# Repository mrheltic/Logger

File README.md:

# Logger

## 📝 Table of Contents
- [About](#🧐-about)
- [Getting Started](#🏁-getting-started)
- [Hardware](#🔧-hardware-required)
- [Description](#description)
- [Theoretical Notions](#theoretical-notions)
- [Code](#⌨️-code)
- [Display Mode](#🖥️-display-mode)
- [SD Mode](#💾-sd-mode)
- [Serial Mode](#💻-serial-mode)
- [Built using](#⛏️-built-using)
- [Contributing](#🫂-contributing)
- [Authors](#✍️-authors)
- [Repo Activity](#repo-activity)
- [License](#license)
- [Acknowledgments](#🎉-acknowledgments)

## 🧐 About
This project is a data acquisition system built using an ESP32 microcontroller board. The system incorporates an ADS1115 analog-to-digital converter, an SSD1306 display, and three buttons for user interaction. It is designed to store data on an SD card or send it to a pc for further analysis.

### Features

- Acquisition of analog sensor data using ADS1115 ADC
- Real-time display of sensor readings on SSD1306 OLED display
- User interaction through three buttons for control and configuration
- Storage of acquired data on an SD card for offline access
- Transmission of data to a computer for centralized analysis

## 🔧 Hardware Required

## 🏁 Getting Started

### Prerequisites

- Arduino IDE or Visual Studio Code (with PlatformIO)
- ESP32 board manager for Arduino IDE
- Libraries:
  - Adafruit ADS1X15 (for ADS1115)
  - Adafruit SSD1306 (for SSD1306 display)
  - SD (for SD card storage)
  - <other libraries as required>

### Installation

<details open>
<summary><i>Installation using Arduino IDE</i></summary>

- Clone or download the project repository from GitHub.
- Open the Arduino IDE and install the ESP32 board manager if not already installed.
- Connect the hardware components as per the provided circuit diagram.
- Install the required libraries using the Arduino Library Manager.
- Upload the code to the ESP32 board using the Arduino IDE.
- Monitor the serial output to ensure successful connection to the sensors.
- Verify the functionality by checking the sensor readings on the SSD1306 display and the data storage on the SD card.
</details>

<details open>
<summary><i>Installation using Visual Studio Code</i></summary>

- Clone or download the project repository from GitHub.
- Open VS and compile the software (changing the details on platform.ini according to your hardware).
- Connect the hardware components as per the provided circuit diagram.
- Upload the code to the ESP32 board using the upload tool.
- Monitor the serial output to ensure successful connection to the sensors.
- Verify the functionality by checking the sensor readings on the SSD1306 display and the data storage on the SD card.

</details>

## Description

## ⌨️ Code

All the code was written using the arduino Framework, for an ESP32. This gave us significant advantages in terms of ease of writing, online documentation, and especially in terms of click-through, which is considerably greater than for an arduino Uno. We followed a kind of MVC model, where each component is separate from the others and deals only with the things it is responsible for, invoking higher-level primitives. This allowed us to manage different components more smoothly.

### Main

The main substantially is a method wrapper and deals at a higher level with handling scrolling through the various menus. Initially (in setup) it asks the controller to initialize devices (the basic ones, such as buttons, screen, ...)

```cpp
while (!initializeDevices()){
}

updateMenu();
```

After this handles menu selection

```cpp
if (stateMenu)
{
  if (goDown())
  {
    menu++;
  }
  if (goUp())
  {
    menu--;
  }
  if (select())
  {
    executeAction(); //Enters in the selected menu
  }
}
```

### Controller

The controller is the component that manages all component behavior and is directly responsible for making measurements. Besides that it initializes all the devices and the serial. The initializations that are done can be blocking or non-blocking, depending on the type of component we want to initialize: a failure of the fundamental components results in a program block inside a loop, which will not allow the execution of the remaining code, while the other components may not be initialized at all. The reference with respect to the success or failure of initialization we have it by returning a boolean value true when the method is terminated, so it does not take into account subsequent failures. The whole initial part is devoted to declaring all pins connected to the board, and in case of custom configurations they can be changed before compilation. 

After all parameters have been selected, data acquisition will proceed. This involves an initial setup phase, in which, based on what parameters are selected (saved as global variables in the controller) it will go to set the mode (and consequently the channels to read from), the data rate, and calculate gain and offset. Depending on the output selected it could change significantly, but we will also have an output on the serial that tells us what is happening. Also in this part I am going to initialize the measurement object, which will handle the calculations made for mean and std.

```cpp
void adcSetup()
{
  setRate(currentSampleRate); //Physically setting the sample rate with ADS function
  setChannel(); //Setting the channel, gain and other useful parameters

  K_value = calculateCoefficient();
  O_value = calculateOffset();

  Measurement measurement(currentSampleRate); //Instantiate the object
}
```

After running the setup you enter the loggerAct, which is the method that takes care of the measurement. Here, depending on the mode that will be selected it will have different behavior, but basically what it does is:

```cpp
// The microcontroller is waiting for an interrupt from the ADC
if (!new_data)
  {
    return;
  }

// When the adc is alerted via the alert pin the code continues

if (!measurement.isArrayFull())
  {
    measurement.insertMeasurement(adcValue); // Get the misuration and stores in the array
  }

else
  {
    measurement.setArrayFull(false); // Empties the array and compute mean and std
    loggerGraphic(mode, channel, timestamp, mean); // Print on display the parameters
  }

new_data = false;
```

### View

The view component deals with screen management. Here it is initialized and passing it the necessary parameters updates the screen. Bipmap images of the various modes and associated sliders are also saved here. The view also provides functions to be used directly by the controller, such as the one used during the loggerAct, which takes care of printing media (for each second), timestamp, mode, and output

### Model

The model is the component that manages the "measurements" class and takes care of the array. This provides various functions to calculate different values useful for measurements, such as mean and standard deviation. In fact, when we go to initialize the object an array is created, of length equal to the data rate, and we go to calculate mean and std for each second. Each time the adc returns us the value, from the controller, we go to invoke a function that is used to insert the measured value (already possibly multiplied by the gain and summed with the offset) at the tail of the array. 

```cpp
class Measurement
{
private:
    int *measurements;
    float mean;
    float std; 
    bool arrayFull;

public:
    Measurement(int len);
    ~Measurement();
    void insertMeasurement(int value);
    void calculateMean();
    void calculateStd();
    void reset();
    bool isArrayFull();
    int getLength();
};
```

## Theoretical Notions
<details open>
<summary><i>Adc</i></summary>
In this project we use the ADS1115 that is a very small, low-power, 16-bit, delta-sigma (ΔΣ) analog-to-digital converters (ADCs).
There are many ADCs available on the market for various applications: Ramping, SAR, delta-sigma, Flash and so on. 
ΔΣ ADCs are now ideal for converting analog signals over a wide range of frequencies, from DC to several megahertz. Basically, these converters consist of an oversampling modulator followed by a digital filter that together produce a high-resolution data-stream output. The ADS1115 has an adjustable gain(PGA), an interal voltage reference, a clock oscillator, an I2C interface, and also a programmable digital comparator that provides an alert on a dedicated pin. The latter played an important role in carrying out the sampling at the maximum achievable speed of 860SPS. Thanks to the mux the adc has four single-ended(to measure
each channel with respect to ground) or two differential inputs and two available conversion mode: single-shot mode(power saving mode) and continuous mode. In continuous conversion mode, the adc automatically begins a conversion of the input as soon as the previous conversion is completed and the rate is programmed by software.
To achieve high accuracy measurements it's a mandatory following several step:

- Use the Maximum Resolution in the readings
- Adjust the PGA to match the voltage range of your input signal(all specifications can be found in the datasheet)
- Use an external voltage reference instead of the integrated
- Implement appropriate filtering and signal conditioning techniques to minimize noise and Interference
- Periodically calibrate the system to compensate any drift
- Avoid common source of error such as impedance mismatches
- Select data rate based on dynamic meausurements or slow signals
- Minimize signal path lengths.
</details>

## 🖥️ Display Mode

### Usage

### Performance Evaluation

## 💾 SD Mode

### Usage

### Performance Evaluation

## 💻 Serial Mode

### Usage

### Explanation

In the data acquisition stage, data is sent to the pc, which is processed through python. The manufacturer of the module, in the datasheet indicates that the conversion time is exactly equivalent to 1/DR (worst case: 860SPS), so there will certainly be a small delay due to data processing due to the microcontroller. This, in turn, will have to be added to a time, albeit very small, due to communication via serial. We had initially opted to send the data via the `Serial.println()` function, but this route, following some testing, seemed impractical. This was because, while having a readable result directly from the serial would have made it easy and intuitive to retrieve the data, it introduced a considerable delay, far in excess of the 1/DR value, even orders of magnitude (about tenths of a second). We therefore opted for the `Serial.write()` function, but again there were problems, since the measured values are 16-bit integers, so they needed to be split in two and sent (so as to send 8 bits at a time). 

```cpp
Serial.write(0xCC);                   // Start byte
Serial.write((ADCvalue >> 8) & 0xFF); // High byte
Serial.write(ADCvalue & 0xFF);       // Low byte
```
- `Serial.write(0xCC)` sends a start byte. The Serial.write() function writes binary data to the serial port. 0xCC is the hexadecimal representation of the start byte. The microcontroller need to send this to communicate that a new set of data is starting.

- `Serial.write((ADCvalue >> 8) & 0xFF)` sends the high byte of ADCvalue. The >> 8 operation shifts the bits of ADCvalue 8 places to the right, effectively moving the high byte to the position of the low byte. The & 0xFF operation then masks the lower byte, so only the original high byte of ADCvalue remains.

- `Serial.write(ADCvalue & 0xFF)` sends the low byte of ADCvalue. The & 0xFF operation masks the high byte of ADCvalue, so only the low byte remains.

After the microcontroller sends the measured value this way, python will have to deal with reconstructing it and converting it to a readable value, like this:

```python
start_byte = ser.read(1)  # Read the start byte
    if start_byte == b'\xCC':  # Verify the start byte
        high_byte = ser.read(1)  # Read the high byte
        low_byte = ser.read(1)  # Read the low byte
        measurement = (ord(high_byte) << 8) | ord(low_byte)  # Merge the bytes
```

- `start_byte = ser.read(1)` reads one byte from the serial port and assigns it to the variable start_byte.

- `if start_byte == b'\xCC'` checks if the start byte is equal to b'\xCC', which is the byte representation of the hexadecimal number 0xCC. If the start byte is 0xCC, the code inside the if statement will be executed. This is used to verify that the data transmission is starting correctly.

- `high_byte = ser.read(1)` reads the next byte (after the start byte) from the serial port, which is the high byte of the measurement.

- `low_byte = ser.read(1)` reads the next byte from the serial port, which is the low byte of the measurement.

- `measurement = (ord(high_byte) << 8) | ord(low_byte)` merges the high byte and the low byte to reconstruct the original measurement. The `ord()` function is used to get the integer value of a byte. The `<< 8` operation shifts the bits of the high byte 8 places to the left, effectively moving it to the position of the high byte in a 16-bit number. The `|` operation is a bitwise OR, which combines the high byte and the low byte into a single 16-bit number.

For more in-depth information you can visit the python code repository directly: [Serial Mode Logger](https://github.com/mrheltic/Serial-Mode-Logger)

### Performance Evaluation

## ⛏️ Built Using
- [PlatformIO](https://platformio.org) - PlatformIO
- [Arduino Framework](https://www.arduino.cc) - Arduino Framework

## 🫂 Contributing

Contributions to this project are welcome. If you encounter any issues or have ideas for improvements, please submit a pull request or open an issue on the project repository.

## ✍️ Authors
- [@mrheltic](https://github.com/mrheltic) - Florio Vincenzo Pio
- [@Phersax](https://github.com/Phersax) - Stasi Francesco
- [@murcie443](https://github.com/murcie443) - Tonti Davide

## Repo Activity

## License
Details about the license.

## 🎉 Acknowledgments
Any acknowledgments (optional).

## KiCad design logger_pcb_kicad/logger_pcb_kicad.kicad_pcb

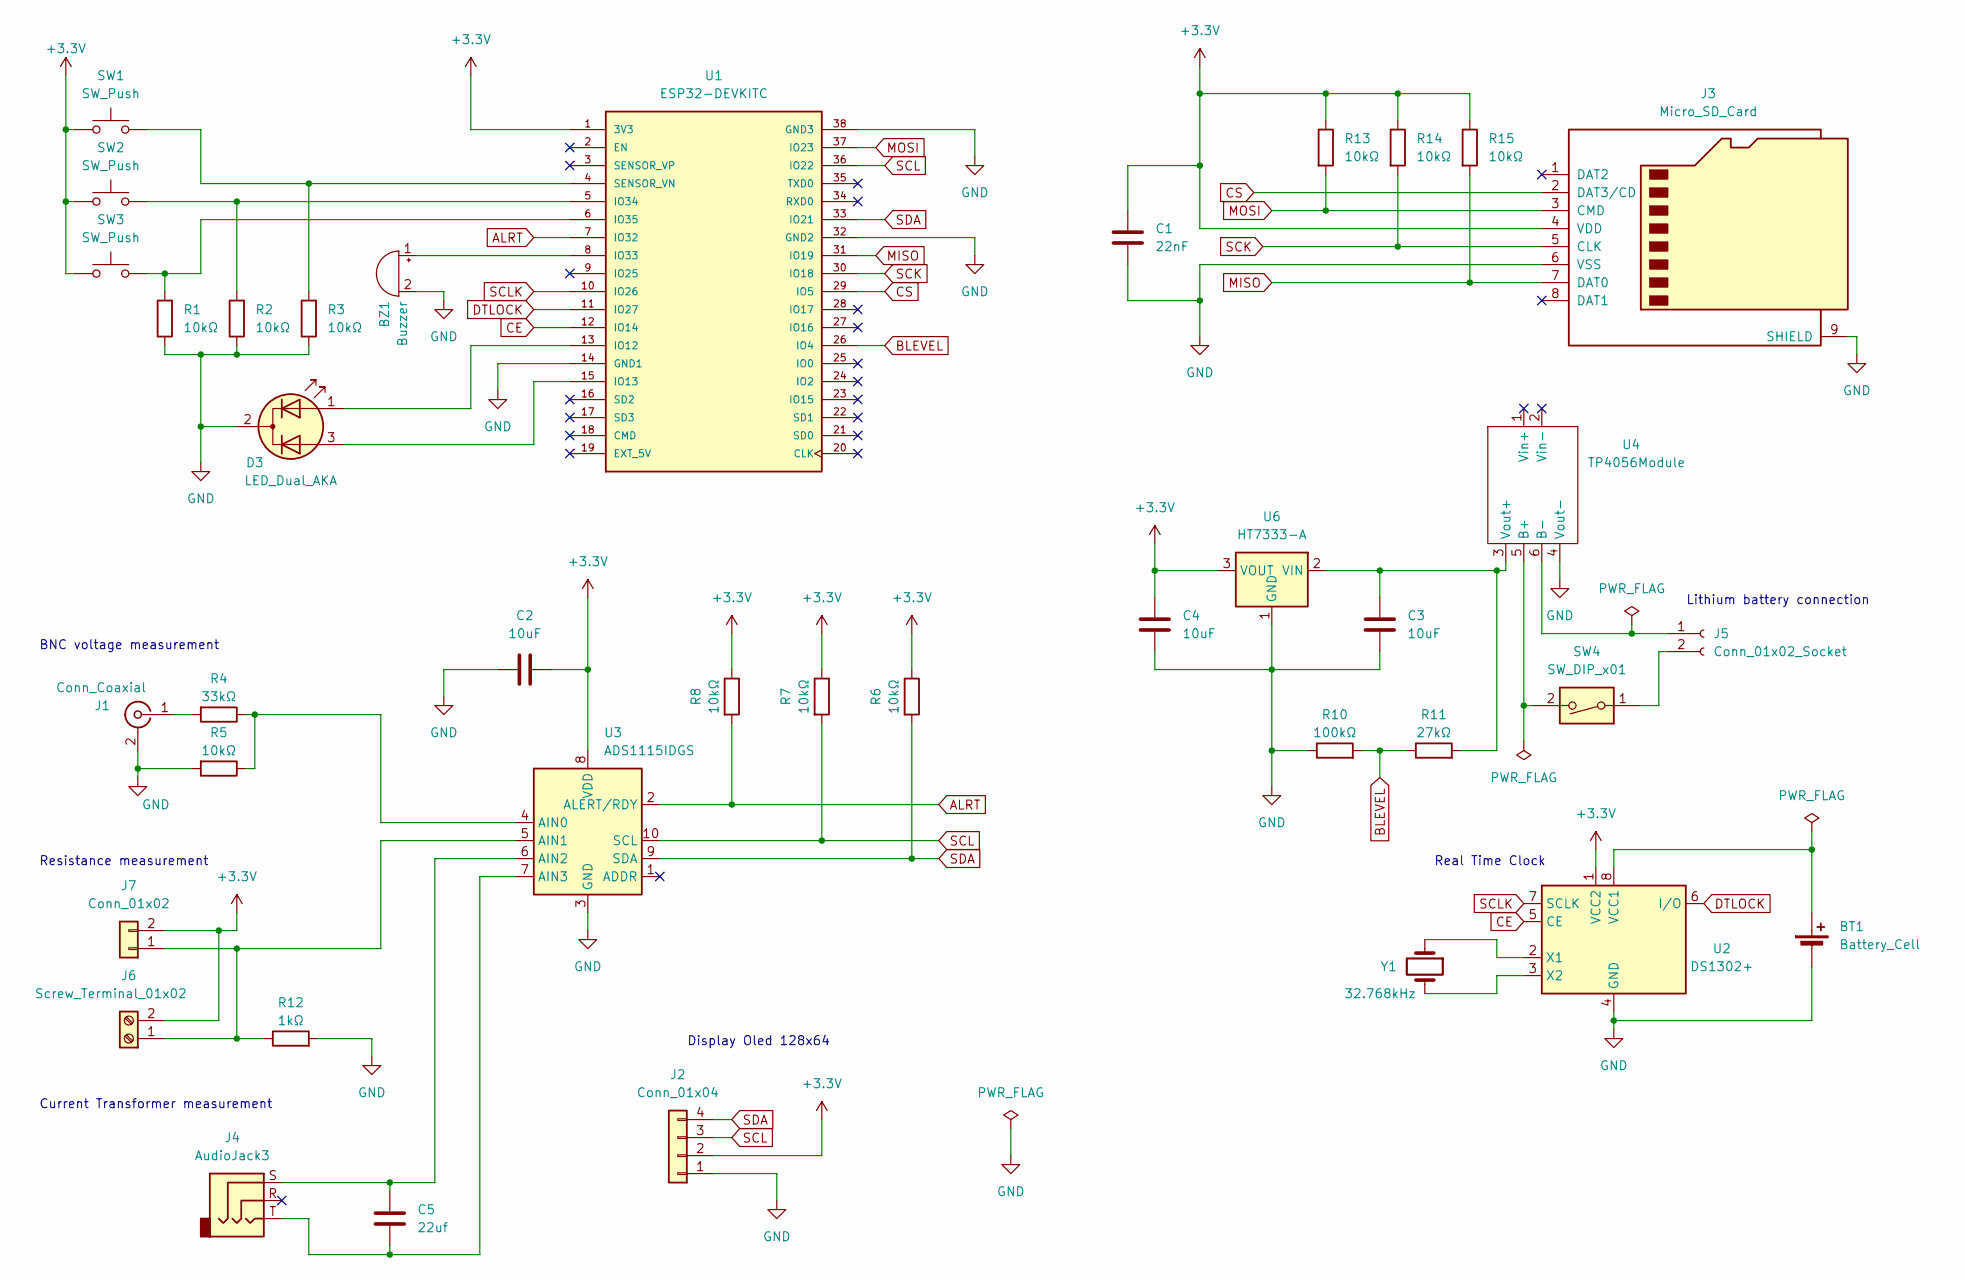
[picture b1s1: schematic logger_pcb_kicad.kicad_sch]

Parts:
BT1: Battery_Cell; Battery_holder_cr2032
BZ1: Buzzer; Buzzer_12x9.5RM7.6
C1: 22nF; C_0805_2012Metric
C2, C3, C4: 10uF; C_0805_2012Metric
C5: 22uf; C_0805_2012Metric
D3: LED_Dual_AKA; LED_D3.0mm-3
J1: Conn_Coaxial; BNC_TEConnectivity_1478035_Horizontal
J2: Conn_01x04; 128x64OLED
J3: Micro_SD_Card; J_SD_Card-micro_socket_A
J4: AudioJack3; Jack_3.5mm_CUI_SJ1-3525N_Horizontal
J5: Conn_01x02_Socket; JST_EH_B2B-EH-A_1x02_P2.50mm_Vertical
J6: Screw_Terminal_01x02; TerminalBlock_Altech_AK300-2_P5.00mm
J7: Conn_01x02; PinHeader_1x02_P2.54mm_Vertical
R1, R2, R3, R6, R7, R8, R13, R14, R15: 10kΩ; R_1206_3216Metric
R4: 33kΩ; R_Axial_DIN0207_L6.3mm_D2.5mm_P10.16mm_Horizontal
R5: 10kΩ; R_Axial_DIN0207_L6.3mm_D2.5mm_P10.16mm_Horizontal
R10: 100kΩ; R_Axial_DIN0207_L6.3mm_D2.5mm_P10.16mm_Horizontal
R11: 27kΩ; R_Axial_DIN0207_L6.3mm_D2.5mm_P10.16mm_Horizontal
R12: 1kΩ; R_Axial_DIN0207_L6.3mm_D2.5mm_P10.16mm_Horizontal
SW1, SW2, SW3: SW_Push; SW_PUSH-12mm
SW4: SW_DIP_x01; SW_CuK_JS202011AQN_DPDT_Angled
U1: ESP32-DEVKITC; MODULE_ESP32-DEVKITC; PARTREV N/A
U2: DS1302+; DIP-8_W7.62mm
U3: ADS1115IDGS; TSSOP-10_3x3mm_P0.5mm
U4: TP4056Module; TP4056-18650
U6: HT7333-A; SOT-89-3
Y1: 32.768kHz; Crystal_C38-LF_D3.0mm_L8.0mm_Horizontal

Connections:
+3.3V: C1.1, C2.1, C4.1, J2.2, J3.4 (VDD), J6.2, J7.2, R6.1, R7.1, R8.1, R13.1, R14.1, R15.1, SW1.1, SW2.1, SW3.1, U1.1 (3V3), U2.1 (VCC2), U3.8 (VDD), U6.3 (VOUT)
ALRT: R8.2, U1.7 (IO32), U3.2 (ALERT/RDY)
BLEVEL: R10.2, R11.1, U1.26 (IO4)
CE: U1.12 (IO14), U2.5 (CE)
CS: J3.2 (DAT3/CD), U1.29 (IO5)
DTLOCK: U1.11 (IO27), U2.6 (I/O)
GND: BT1.2 (-), BZ1.2 (+), C1.2, C2.2, C3.2, C4.2, D3.2 (K), J1.2 (Ext), J2.1, J3.6 (VSS), J3.9 (SHIELD), R1.1, R2.1, R3.1, R5.2, R10.1, R12.2, U1.14 (GND1), U1.32 (GND2), U1.38 (GND3), U2.4 (GND), U3.3 (GND), U4.4 (Vout-), U6.1 (GND)
MISO: J3.7 (DAT0), R15.2, U1.31 (IO19)
MOSI: J3.3 (CMD), R13.2, U1.37 (IO23)
unnamed: BT1.1 (+), U2.8 (VCC1)
unnamed: BZ1.1 (-), U1.8 (IO33)
unnamed: D3.1 (A1), U1.13 (IO12)
unnamed: D3.3 (A2), U1.15 (IO13)
unnamed: J1.1 (In), R4.2
unnamed: J5.1, U4.6 (B-)
unnamed: J5.2, SW4.1
unnamed: J6.1, J7.1, R12.1, U3.5 (AIN1)
unnamed: R2.2, SW2.2, U1.5 (IO34)
unnamed: R1.2, SW3.2, U1.6 (IO35)
unnamed: R3.2, SW1.2, U1.4 (SENSOR_VN)
unnamed: U2.2 (X1), Y1.1
unnamed: U2.3 (X2), Y1.2
unnamed: R4.1, R5.1, U3.4 (AIN0)
unnamed: C5.1, J4.S, U3.6 (AIN2)
unnamed: C5.2, J4.T, U3.7 (AIN3)
unnamed: SW4.2, U4.5 (B+)
unnamed: C3.1, R11.2, U4.3 (Vout+), U6.2 (VIN)
SCK: J3.5 (CLK), R14.2, U1.30 (IO18)
SCL: J2.3, R7.2, U1.36 (IO22), U3.10 (SCL)
SCLK: U1.10 (IO26), U2.7 (SCLK)
SDA: J2.4, R6.2, U1.33 (IO21), U3.9 (SDA)

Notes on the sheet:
BNC voltage measurement
Real Time Clock
Current Transformer measurement
Resistance measurement
Display Oled 128x64
Lithium battery connection

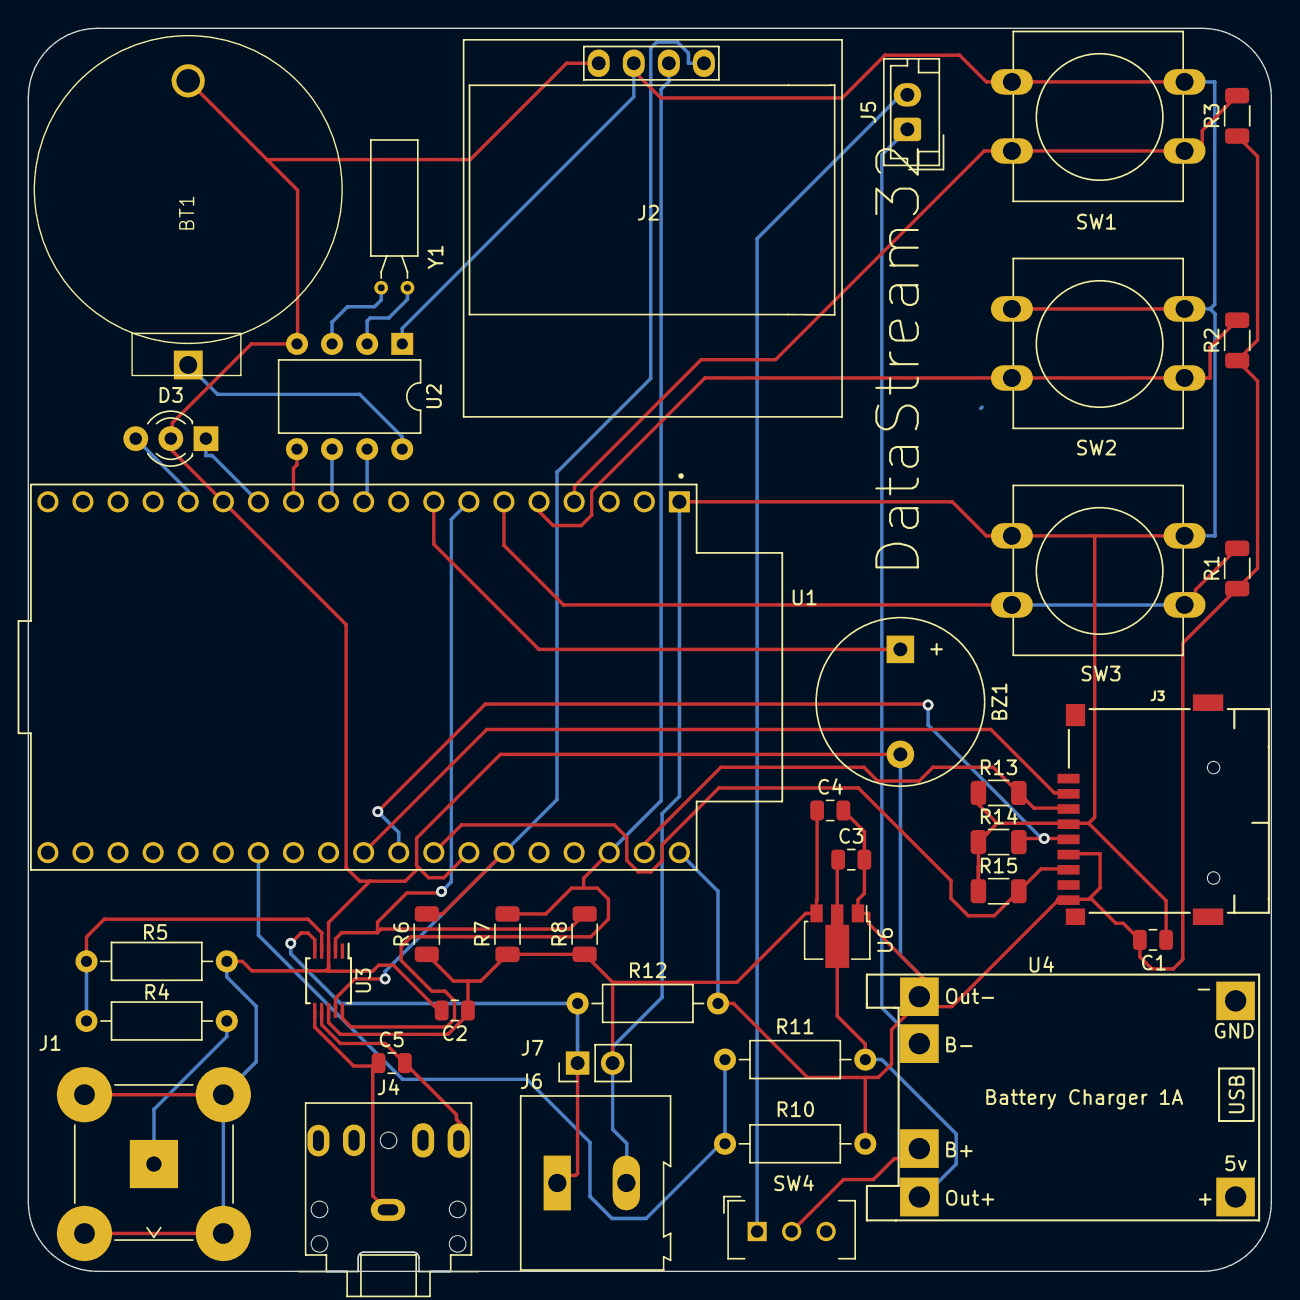
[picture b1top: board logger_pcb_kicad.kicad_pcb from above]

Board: 2 copper layers, 90.0 x 90.0 mm, 39 parts (0 on the bottom side), 31 nets.

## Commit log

2023-10-24 Init
    Added:
    -Initialized platform.ini
    -Blinking test
    -Declared variables in main
2023-10-24 v0.0.1
2023-10-24 Added pio and .ini to gitignore
2023-10-24 added pio to gitignore
2023-10-24 Restored gitignore
2023-10-24 test push
2023-10-24 Removed libdeps and build folders
2023-10-25 v0.1.0
    Added OLED screen
2023-10-26 v0.1.1
    Added ADS initialization
    Added debug printing on display and serial
    Refactoring
2023-10-26 v0.1.1
    Added readme and pinout
2023-10-27 Fixed gitignore
2023-10-27 Revert "Fixed gitignore"
    This reverts commit 6d24c08ace557a229f18ffe79bf65c35de1f0625.
2023-10-28 Update platformio.ini
    Added library dependencies
2023-11-09 display init
    added:
    menu structure
    bitmap menu
    bitmap input e output mode
    basic menu navigation in the loop
2023-11-10 Added MVC Logic
2023-11-11 Loop structure
    Loop structure
    variable state
    fixed some functions
2023-11-11 v0.2.0
    Added:
    graphic functions
    action functions
    menu structure
    submenu sample rate set
2023-11-13 v0.2.1
    Some functions have been renamed.
    Submenus have been created to select the input and output modes.
    The delay after button presses has been entered into the soundBuzzerScroll() and soundBuzzerSelect() functions.
2023-11-14 main update
2023-11-14 RTC Introduction
    added:
    RTC Library and Initialization
    some bitmap
2023-11-14 inizialize RTC
    inizialize RTC
2023-11-15 Added Support to ESP8266
2023-11-15 Updated dependencies
2023-11-16 logger graphic
    added logger graphic
2023-11-17 Code organization
2023-11-17 Updated board
    ESP32 <- nodeMCU v3 (ESP12-E)
2023-11-17 Update platformio.ini
    ESP32 <- nodeMCU v3 (ESP12-E)
2023-11-17 Updated Settings and gitignore
2023-11-17 v0.2.2
    -Board change
    -Added toString method for setting Rate
    -Organized headers
2023-11-18 Added website pages
2023-11-21 Sub setup
    Introduction of the boolean variable for the submenu setup
2023-11-22 infoGraphic()
    Added the graphics of the "info" submenu
2023-12-02 Added documentation💀
2023-12-02 Model implementing
2023-12-03 gitignore Updated
2023-12-03 gitingnore Updated
2023-12-03 Initialized branch
2023-12-04 Updated .gitignore
2023-12-05 a0.2.3
    Added:
    -Measurements test
    -Added Serial commands
    -Started to take adc values
2023-12-06 b0.2.3
2023-12-06 c0.2.3
2023-12-06 Hotfixes
2023-12-12 General Hotfixes
2023-12-12 General Hotfixes
    - Fixed Differemtial mode
    - Fixed a bug (missing break)
    - Starting to add docs to some revamped function
2023-12-13 d0.2.3
    - Fixed some logical error
    - Removed libs from gitignore
2023-12-13 v0.2.4
    Some fixes:
    - Ads setup
    - Made changes on logic
2023-12-15 Various testing
2023-12-15 Revert "Various testing"
    This reverts commit 208737e370ebb92cc4f04f8f3d67f76d6618f401.
2023-12-15 Implemented RTC
2023-12-15 Init
2023-12-15 only runnuble rtc test
2023-12-17 Added RTC
    RTC has been added and a method for obtaining string format times.
    The loggergraphic function has been changed to receive the string containing the current time
2023-12-17 fixed bug about "channel" and "mode"
2023-12-17 Adjusted serial output
2023-12-17 General Hotfixes
    - Missing semicolons
    - Fixed toString methods
2023-12-17 General Hotfixes
    Added:
    -Array works
    -uint_16 to int
    -Serial from 115200 to 250000
2023-12-17 IRAM_ATTR definition
2023-12-17 Added serial control for new data
2023-12-18 Very important update in the logger code!!!!!!!!!!!
    Changed:
    -Data rate setting (TODO)
    -Fixed general bugs on timings
2023-12-18 0.3.0
2023-12-19 v0.3.1
    added:
    -SPI comunication library
    -SD function for storage data in .txt file
2023-12-19 v0.3.1
    - Changed documentation based on logical changes
    - Changed system to calculate mean (now the sum is incremented for every iteration directly)
2023-12-19 Revert "Co-authored-by: dav01luffy <dav01luffy@users.noreply.github.com>"
    This reverts commit 52559b9f94277b24b1968871d376b47ae81394ab, reversing
    changes made to ef256c03d0432c210b413ccbfa4b5324dc4ea9b2.
2023-12-19 v0.3.2
    Added switch case to select mode
2023-12-19 Updated model
2023-12-19 Fixes
    -delete useless lines
2023-12-20 error graphic funtion and device control
2023-12-22 Implemented new model logic
2023-12-22 Test on writing single measurements
2023-12-22 Updated gitignore
2023-12-23 v0.3.2
    added:
    -function to preliminary control in logger sub-menu
    -SD begin
    -SPI begin
    ATTENTION: micro sd not working
2023-12-23 Added libaries
2023-12-23 Fixed libraries
2023-12-23 v0.3.3
    Added:
    -Gain function
    -Offset function
2023-12-23 Testing
2023-12-24 v0.3.4
    Problema SD risolto (attenzione alla libreria ledc)
    Primo test di misura in tensione
    Aggiornata la funzione loggerGraphic()
2023-12-27 Test for the measure in current
    added:
    -Calculation of constant variables for measurement
    -Current measurement test
    -Update ADS setup
2024-02-19 Improved readability
2024-02-19 Testing readability
2024-02-19 Fixed links
2024-02-19 Added descriptions to readme
2024-02-19 Implemented tests
2024-02-20 Generalized data rate
2024-02-20 Fixing stuffs
2024-02-20 Fixed indendations
2024-02-20 test
2024-02-20 Removed initial loop
2024-02-20 v0.4.0
    - Added Serial
    - Fixed controller
2024-02-20 Fixed declaration problems
2024-02-20 v1.0.0a
2024-02-20 Added docs
    I'm tired D;
2024-02-21 Added new bitmaps for serial mode
2024-02-21 Changed the char sended to python
2024-02-21 Added badges
2024-02-21 Fixed Buzzer
    -Correct the buzzer pin
    -Adding Function for Buzzer and variables to manage the sound
2024-02-21 readme adc
    -add brief summary
2024-02-21 readme
    fix
2024-02-21 Added main and controller in readme
2024-02-21 Added docs
2024-02-21 Added model and view
2024-02-22 update readme
    -fixes
    -add input configuration
2024-02-22 fixx
2024-02-22 add a section
2024-02-22 v1.0.1
    added:
    -loggeract functions
    -coefficients to convert voltage measure
    -fixed some problem with Serial and SD mode
2024-02-22 control result and problems
2024-02-22 Added istructions for serial
2024-02-23 v1.1.0
2024-02-23 Resistance measurement graphics
2024-02-23 Timeout declaration for serial response limit
    added:
    -Timeout declaration for serial response limit
    -Graphics display errors
    -Exception management in preliminarycontrol ()
2024-02-23 DS1302 setTime example
    Updated the Arduino sketch to set time on DS1302
2024-02-24 Added parameters for measure convertion
2024-02-27 Adjust method to send parameters on serial
    -Fixed preliminary functions
    -Fixed graphic functions
2024-02-29 Files gerber for pcb added
2024-02-29 update serial
    add timestamp
2024-02-29 V1.1.1
    Fixed serial (sending timestamp)
    Raised time before closing serial
2024-02-29 info graphic added
2024-03-10 logger pcb files
2024-03-13 Added .ds32
2024-03-14 Added photos
2024-03-15 Added fft
2024-03-15 Added images
2024-03-16 Hotfix
2024-03-17 Added graphs
2024-03-17 Create LICENSE
2024-03-17 Removed useless files
2024-03-18 Picture update
2024-03-18 Updated photos with timestamp
2024-03-19 New bitmap
2024-03-19 fix controlResult + comment
2024-03-20 changed baud rate to 115200
    --can be sufficient for the conversion and at the same time be used with the wsl1 on windows
2024-03-21 Fixed preliminary control function
    Fixed preliminary control function and some graphic settings
2024-03-23 improved communication delay
2024-03-23 Revert
2024-03-23 Revert to stable version
2024-03-23 v1.2.0
2024-04-03 fix fft images
2024-04-03 Fixed pics
